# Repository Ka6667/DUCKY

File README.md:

# DUCKY

## Table of Contents
* [What is DUCKY?](#what-is-ducky)
* [Why did I build it?](#why-did-i-build-it)
* [How to use DUCKY](#how-to-use-ducky)
* [Schematics](#schematics)
* [PCB Design](#pcb-design)
* [Assembly Instructions](#assembly-instructions)
* [3D Model](#3d-model)
* [BOM](#bom)
---

## What is DUCKY?
Ducky is my custom smart alarm and personal assistant!
Ducky lives on a little screen and she takes her job very seriously. She can set a time. if you ignore her alarm, and she will absolutely let you know she's disappointed. She's got feelings, okay?!!!!
When you want to listen to music, Ducky can help you with. When it's late at night, she's already sleeping, because unlike you, she has great sleep hygiene. And when you actually wake up on time? She will be so happy so don't let her down.
I used xiao esp32c, a tiny TFT screen, and way too much love to design it, Ducky is a smart alarm clock, timer, stopwatch, and music companion all in one. She syncs her time from the internet so she's always right, and she will remind you of that.
## Why did I build it?
I’m constantly missing school because my old alarm is totally unreliable and sometimes it doesn't even go off. I tried buying a new one, but I’m still having the same problem and just can’t seem to wake up. So I’ve decided to build my own smart alarm. I want it to actually interact with me like with changing her mood. let me know if the the time and day, and play music or rain sounds to help me crash at night. Basically, it’s going to be a calendar and my music box, and 100% better at getting me out of bed on time with her loud alarm sound!.

## How to use DUCKY?
Clock Mode is the default. She shows the time and date.<br>
During the day she blinks happily. After 10 PM she goes to sleep.<br>
Press once → Timer Mode<br>
Turn the knob to pick minutes, then press again to start.<br>
If the alarm fires and you don't respond in 30 seconds, she gets sad  <br>
Press twice quickly → Stopwatch Mode<br>
Press to start and stop. Turn the knob to set a lap alert interval.<br>
Hold for 0.5 seconds → Music Mode<br>
Press to play or pause. Turn the knob to change the volume.<br>
Hold for 2 seconds → Go back to Clock Mode from anywhere.<br>
The knob always does something useful depending on the mode, brightness in clock mode, minutes in timer, lap interval in stopwatch, and volume in music mode.<br>
The music is saved in the SD Card of the DFplayer!! make sure to download the music and the loudest alarm sound on the SD card or Ducky will be silent the whole time!<br>
## Schematics

## PCB Design

## Assembly Instructions
it is so simple just add four screws to the four mounting holes inside the case to attach the PCB to the case as you can see here (just use Socket Head Cap Screws):

Then there are three screws for the outer mounting for the face of the case. I extened the holes a little bit outside the case to make it more stable (also use Socket Head Cap Screws):

you can still use a washer if you want to install any other screws that has small heads. just make sure to keep everything fixed in its place!! 

## 3D Model

The small little cylinder on the right side is a body that will be used as a knob extender for the potentiometer (The hole on the side and the knob's postition, lenght and width are accurate based on the data sheet of the potentiometer)! The CAD desgin of the potentiometer is not present because I can't find a good one that will really looks like the real potentiometer that I will use in this project (it's not a big deal because I used the potentiometer data sheet to know the exact measurements to make the knob and its hole!!!).

## BOM
| Part | Amount | Price | Link |
| :--- | :---: | :---: | :--- |
| XIAO-ESP32C3 | 1 | $11.21 | [Temu Link](https://temu.com/ul/kuiper/un9.html) |
| TFT LCD Display Module | 1 | $7.34 | [Amazon Link](https://www.amazon.eg/-/en/TFT-Display-Module-Interface-Inch/dp/B0CJ851LDT/) |
| DFPlayer Mini MP3 | 1 | $2.54 | [Temu Link](https://www.temu.com/ul/kuiper/un9.html) |
| Speakers | 1 | $4.94 | [Temu Link](https://www.temu.com/ul/kuiper/un9.html) |
| LIPO-Battery | 1 | $1.10 | [Makers Electronics Link](https://makerselectronics.com/product/rechargeable-400925-lipo-battery/) |
| 1000K Ohm resistor | 1 | $0.05 | [Amazon Link](https://www.amazon.eg/-/en/Resistor-1K-ohm-4W-2pcs/dp/B0CJQ3M5J1/) |
| Screws | 4 | $1.50 | [Temu Link](https://www.temu.com/ul/kuiper/un9.html) |
| Push-buttons | 1 | $0.04 | [Temu Link](https://www.temu.com/eg-en/10pcs-6x6x5mm--tactile-tact-push-button-micro-switch-mini-micro-momentary-tactile-push-button-switch--x-5mm-g-605681855863393.html) |
| Potentiometer | 1 | $0.34 | [Amazon Link](https://www.amazon.eg/-/en/Generic-414999-483-Potentiometer-10K-Ohm/dp/B091DX3483/) |
| PCB | 1 | $2.00 | [JLCPCB Link](https://cart.jlcpcb.com) |
| **Total** | | **$31.06** <br>*(shipping not included)* | |

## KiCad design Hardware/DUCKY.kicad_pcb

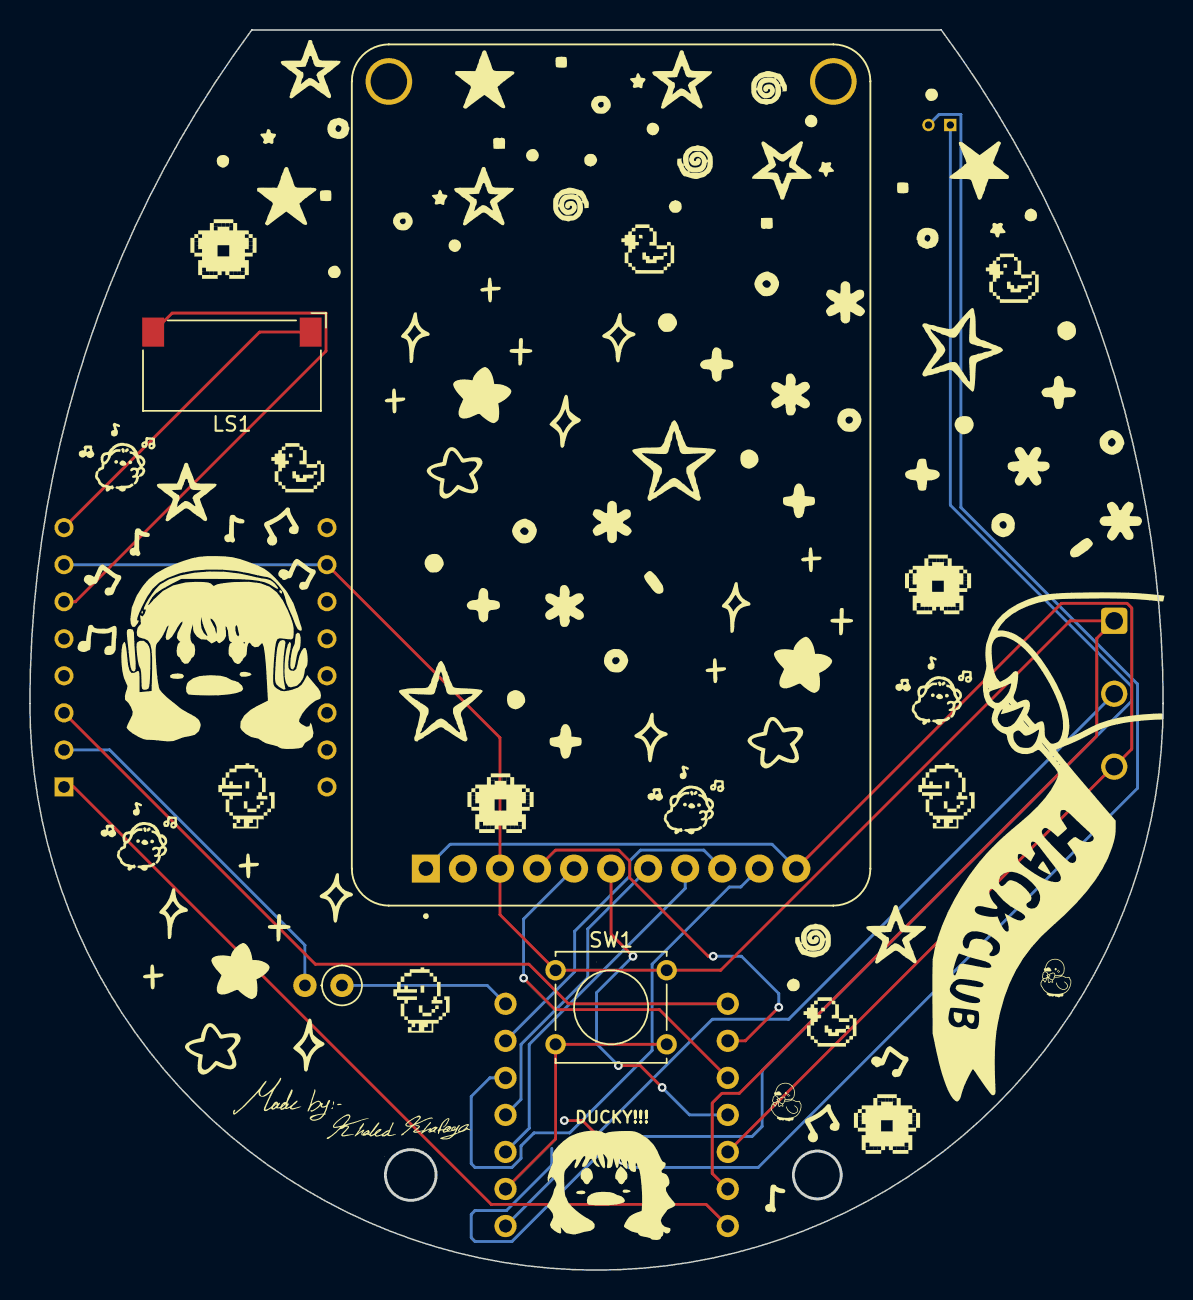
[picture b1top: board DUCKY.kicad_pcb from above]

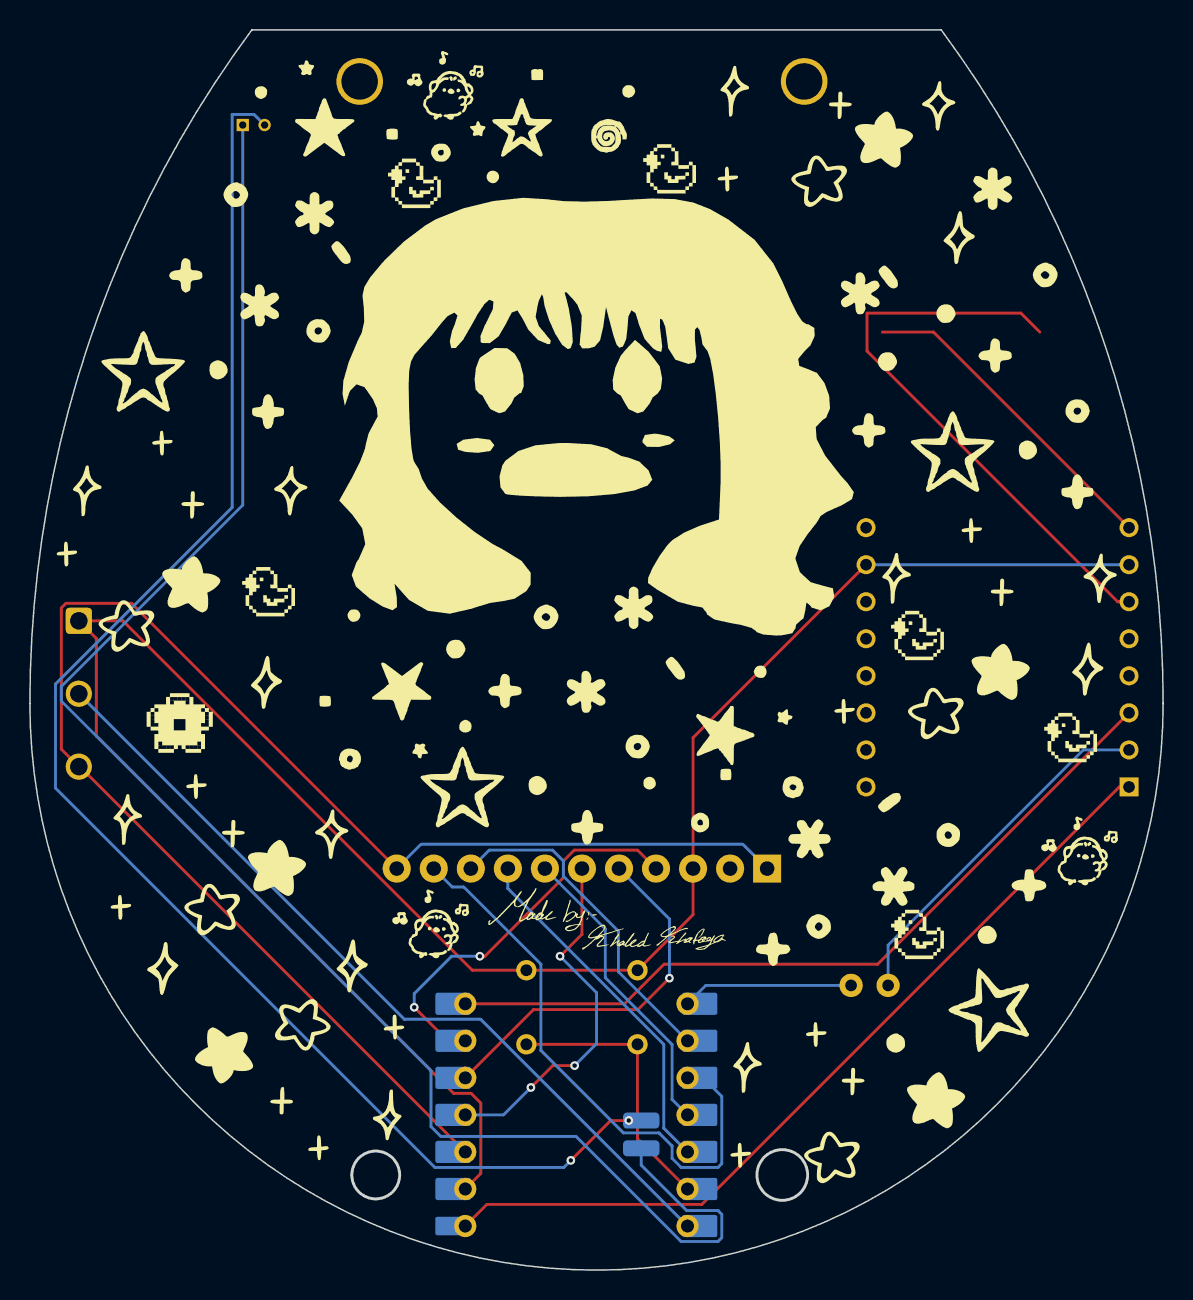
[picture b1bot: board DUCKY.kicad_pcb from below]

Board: 2 copper layers, 77.7 x 85.0 mm, 7 parts (3 on the bottom side), 16 nets.

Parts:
1K1: R_US; R_Axial_DIN0207_L6.3mm_D2.5mm_P2.54mm_Vertical
DS1: 4311; MODULE_4311
LS1: Speaker; Speaker_CUI_CMR-1206S-67
RV1: R_Potentiometer; Potentiometer_Alps_RK097_Single_Horizontal
SW1: SW_Push; SW_Tactile_Straight_KSA0Axx1LFTR
U1: XIAO-ESP32-C3-SMD; XIAO-ESP32-C3-DIP-SMD
U2: DFR0299; MODULE_DFR0299

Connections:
-VSW: DS1.1 (VIN), DS1.11 (BACKLIGHT), RV1.3, U1.12 (3V3), U1.14 (VBUS), U2.1 (VCC)
GND: DS1.3 (GND), RV1.1, SW1.1, U1.13 (GND), U2.7 (GND), U2.10 (GND)
unnamed: DS1.7 (CS), U1.4 (GPIO5_A3_D3)
unnamed: DS1.9 (D/C), U1.6 (GPIO7_D5_SCL)
unnamed: DS1.5 (MISO), U1.10 (GPIO9_D9_MISO)
unnamed: DS1.6 (MOSI), U1.11 (GPIO10_D10_MOSI)
unnamed: DS1.4 (SCK), U1.9 (GPIO8_D8_SCK)
unnamed: DS1.10 (SDCS), U1.5 (GPIO6_D4_SDA)
unnamed: DS1.8 (~RST), U1.3 (GPIO4_A2_D2)
unnamed: RV1.2, U1.1 (GPIO2_A0_D0)
unnamed: SW1.2, U1.2 (GPIO3_A1_D1)
unnamed: U1.8 (GPIO20_D7_RX), U2.3 (TX)
unnamed: 1K1.1, U1.7 (GPIO21_D6_TX)
unnamed: LS1.2, U2.6 (SPK1)
unnamed: LS1.1, U2.8 (SPK2)
unnamed: 1K1.2, U2.2 (RX)

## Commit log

2026-06-20 Create asd
2026-06-20 Create koki
2026-06-20 Create w
2026-06-20 Create s
